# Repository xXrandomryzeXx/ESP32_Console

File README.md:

# ESP32_Console
## Instalation
Following the official documentation from Espressif, you have to setup the standard toolchain for your system:  
[Linux/MacOS](https://docs.espressif.com/projects/esp-idf/en/stable/esp32/get-started/linux-macos-setup.html)  
[Windows](https://docs.espressif.com/projects/esp-idf/en/stable/esp32/get-started/windows-setup.html)  
### Linux/MacOS
After following the documentation you should have the standard toolchain setup.  
Now you can clone the repository. Once inside it, run the command  

`. $HOME/esp/esp-idf/export.sh`  

or for Fish  

`. $HOME/esp/esp-idf/export.fish`  

This will setup the ESP-IDF environment for the project.

Inside the cloned repository should be a directory called `SD_CARD_FILES`.  
Copy its contents to a **Micro SD Card** and format the card to the **FAT32 Format**

After inserting the card into the Micro SD Card Reader, you can build and flash the project to the ESP32  
This is done by performing the following command inside the cloned repository.  

`idf.py build flash monitor`

This will  
1. Build the project
2. Flash it to the ESP
3. Print the debug information to the terminal

### Windows
As I was not developing this on Windows, I don't know how the setup would go for it.

## About
The project was developed as a final assigment for high school. It utilizes the ESP32 to make a console-like game for learning Japanese Kanji.
It consists of multiple components:
1. Custom PCB
2. Node MCU32S board
3. 3.2 Inch TFT SPI Display board
4. Micro SD Card Reader board
5. 4x Push Button
6. 4x 10K resistor
7. Power Swtich
8. Battery box for 3 AAA 1.5V batteries

## The PCB Board
The board is two sided THT. Each component is labeled where it's supposed to be soldered on the board.  
The clean board looks like this  

When attaching the components you have to match their orientation with the text on the silkscreen.  
The populated PCB should look like this

## Game Demonstration
When the console is turned on by the switch in the middle, it will light up and the main menu will show up.  
It displays the Highest achieved score that is saved to the Micro SD Card and also a choice to start a game.  

When you press the corresponding button to the **play** option a new game will begin.  
A question will be generated and the answers selectedd. They will either ask for a  
translation of the kanji displayed or for a reading in japanese.  

If the chosen answer is wrong the game will deduct one life point and will display the  
correct answer for the question.  

Otherwise if the chosen aswer is correct, the game will give 1 point and notify the player  
that the chose answer has been correct.  

The game will end once the player has ran out of lives, there is no way to end a game without
losing unless you power off the console. At the end of a game, the player will be notified
about the score they managed to get. If the score is more than the recorded high score, it will  
be saved as the new highest score.  

## Possible improvements
As this was the first time I ever made something involving a Custom PCB and so many components, I have missed to think about
certain things that could prove beneficial for future projects.

### Cleaner PCB
For a first time design I feel like this one is OK, but for future projects the design should incorporate less prototyping boards and more individual components, like SMD components. These may require more complicated soldering methods but the final product would have a much more professional and clean look.  
Major imporvement would be the use of an independent ESP32 chip that has been flashed with the project.
Another big improvement would come from the TFT display. Instead of using one with a board and pins, an alternative variant that utilises a connector would be better in terms of how thin the console could be.

### Better software
This was also my first time programming on an ESP32 and ESP-IDF, so a lot was figured out through the examples given by Espressif, but the code was not well suited for this project.  
The most improvement that could be done is in the rendering, because the current rendering method is so slow that the FPS is lower than 1, but it can most certainly be at least as good as 10FPS.

### Mounting holes
Mounting holes designed into the PCB could allow for a case to be made for the console, giving it a more solid look and making it a lot more comfortable and safer than the current one, where you hold the PCB and have to take care of what touches the board.

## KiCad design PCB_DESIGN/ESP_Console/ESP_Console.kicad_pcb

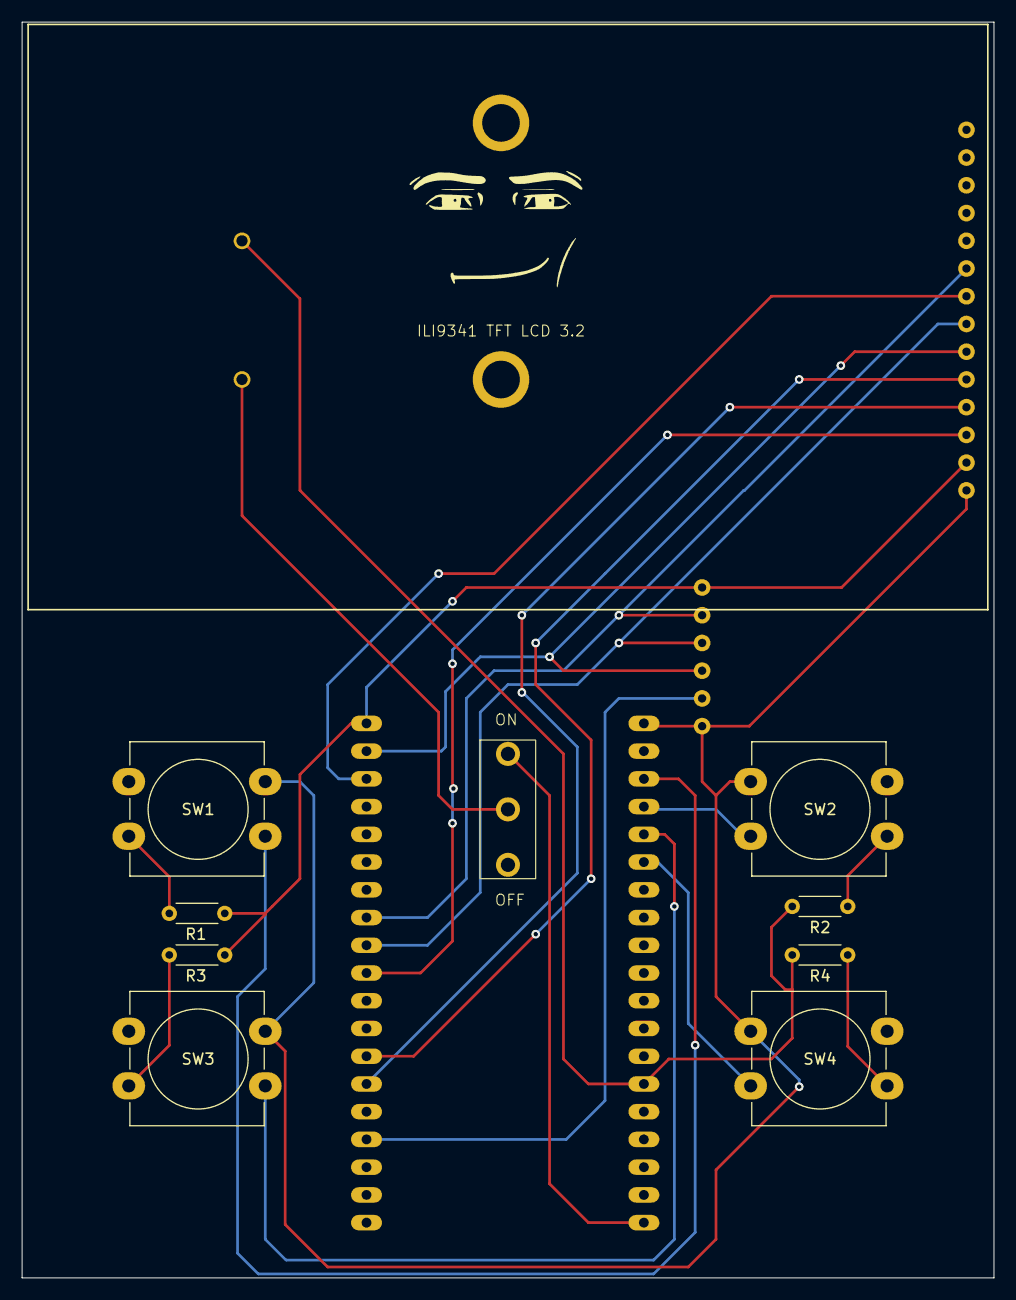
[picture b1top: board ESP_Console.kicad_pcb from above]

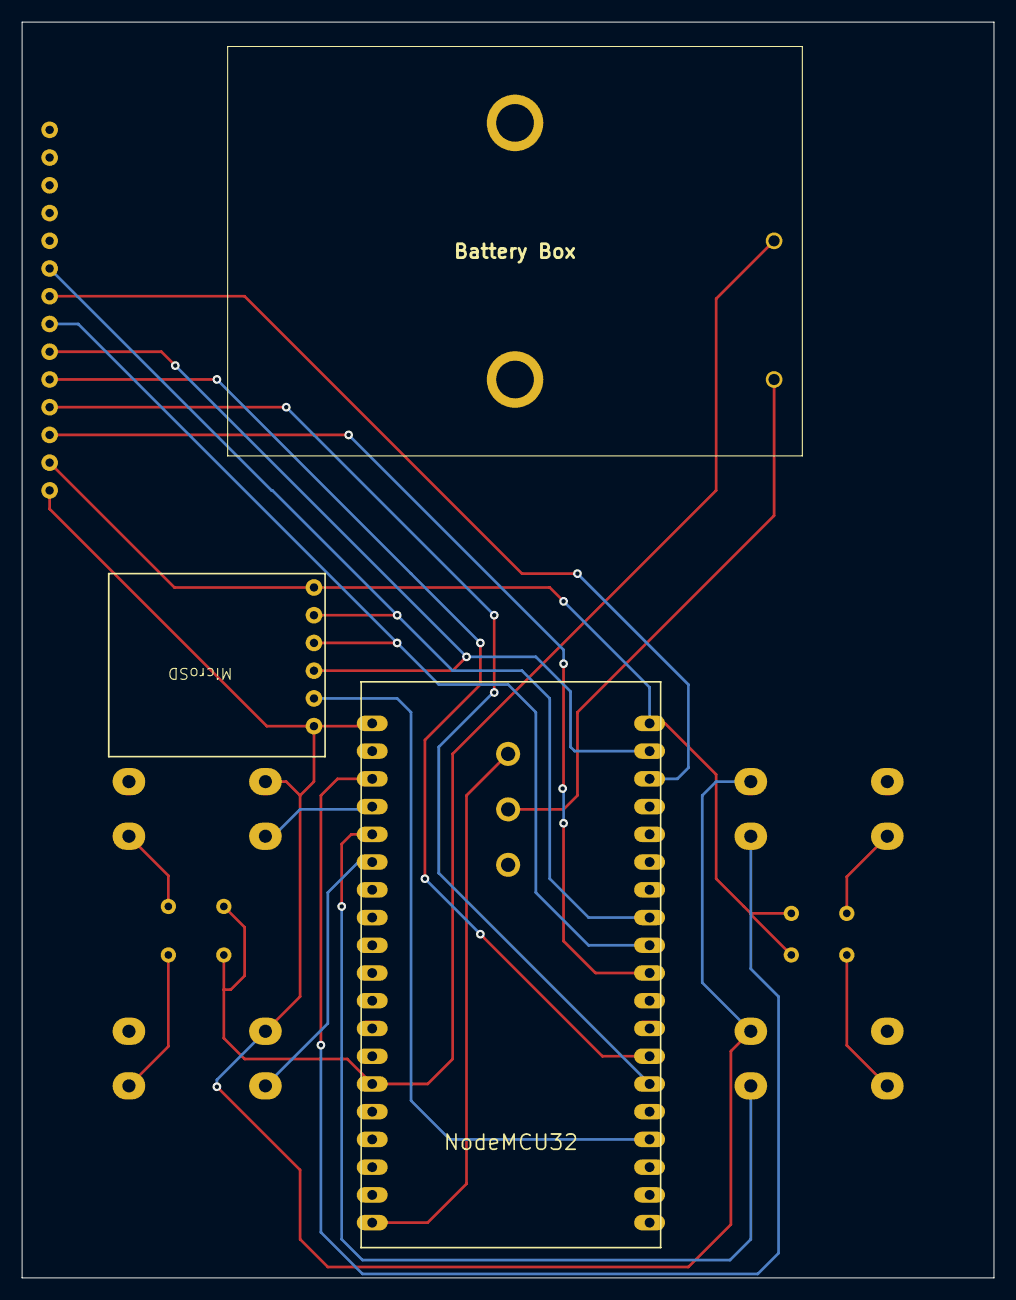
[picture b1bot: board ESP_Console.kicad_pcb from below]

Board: 2 copper layers, 89.0 x 115.0 mm, 13 parts (3 on the bottom side), 17 nets.

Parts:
Battery Box: 2479; 3xAAA battery box 2479
ILI9341 TFT LCD 3.2: 3.2inch SPI Module MSP3218
MicroSD: Micro SD reader module
NodeMCU32: NODEMCU32S
R1, R2, R3, R4: R_US; R_Axial_DIN0204_L3.6mm_D1.6mm_P5.08mm_Horizontal
SW1, SW2, SW3, SW4: SW_Push_Open_Dual; SW_PUSH-12mm_Wuerth-430476085716
SW_1P2T1: SW_1P2T

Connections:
GND: ILI9341 TFT LCD 3.2.2 (GND), MicroSD.6 (GND), NodeMCU32.GND@2, R1.2, R3.2
unnamed: NodeMCU32.GPIO36, R1.1, SW1.2
unnamed: NodeMCU32.GPIO39, R2.1, SW2.2
unnamed: NodeMCU32.GPIO34, R3.1, SW3.2
unnamed: NodeMCU32.GPIO35, R4.1, SW4.2
unnamed: Battery Box.1 (+), SW_1P2T1.1 (VCC)
unnamed: ILI9341 TFT LCD 3.2.1 (VCC), MicroSD.1 (3v3), NodeMCU32.3V3 (3.3V), SW1.1, SW2.1, SW3.1, SW4.1
unnamed: Battery Box.2 (-), NodeMCU32.GND@1, R2.2, R4.2
unnamed: ILI9341 TFT LCD 3.2.7 (SCK), MicroSD.4 (CLK), NodeMCU32.GPIO18
unnamed: MicroSD.2 (CS), NodeMCU32.GPIO15
unnamed: ILI9341 TFT LCD 3.2.9 (MISO), MicroSD.5 (MISO), NodeMCU32.GPIO19
unnamed: ILI9341 TFT LCD 3.2.6 (MOSI), MicroSD.3 (MOSI), NodeMCU32.GPIO23
unnamed: ILI9341 TFT LCD 3.2.3 (CS), NodeMCU32.GPIO5
unnamed: ILI9341 TFT LCD 3.2.5 (DC), NodeMCU32.GPIO4
unnamed: ILI9341 TFT LCD 3.2.8 (LED), NodeMCU32.GPIO22
unnamed: ILI9341 TFT LCD 3.2.4 (RST), NodeMCU32.GPIO0
VCC: NodeMCU32.VIN, SW_1P2T1.2 (Out_1)

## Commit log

2024-02-14 Removed previous README
2024-02-14 Text can be printed on the screen
2024-02-17 Can print out japanese text to the LCD (hiragana only)
2024-02-17 Created game loop and started work on the state machine
2024-02-19 State machine works, loading desired background image from SD is possible
2024-02-22 Started work on Question generation. Don't run yet! It clears the kanji.txt file clean, and I don't know why
2024-03-21 Some code refactoring, new file to handle random number generation. Question generation is not working. The array of answers gets cleared randomly
2024-03-24 Delete build directory
    These files are not needed for building the project, they are generated when the project is built.
2024-03-26 Japanese texts draw without a problem. Parentheses draw in Japanese text cleanly. Question generation is ALMOST done.
2024-03-27 When in the game, the text for the answers will draw in it's respective positions. Needs more work.
2024-03-29 Answering a question creates a new one. Fixed memory leak when loading an image
2024-04-02 Answers in english get pushed to the side of the screen with 20 px padding. Wrong and Right answers are announced with a respective sprite
2024-04-05 All answers have a padding of 20px. There is a counter for the correct answers for the future implementation of the score, some functions have been removed and others have taken their job
2024-04-08 Lives can be tracked. End of game will be reached when the lives reach 0. setState was changed to set_state
2024-04-09 Game loop completes. There is a memory leak that causes the memory to run out after 2 retries. Needs high score to be saved and loaded and the memory leak to be fixed!
2024-04-12 Memory leak fixed! Final score can be viewed at the end of the game. High score save and load is left to be done
2024-04-16 High score load and save complete. Questions use all posible answers, not just the first one
2024-04-16 Removed Quit option from the main menu
2024-04-18 Removed unused code, added descriptions to all functions in the header files
2024-09-17 Fixed the problem where you cannot play another game after finishing one
2024-09-17 Added PCB Design files
2024-09-17 Added pictures for the README
2024-09-18 More pictures for the Readme added
2024-09-18 Rename QuestionFailed.jpg to QuestionWrong.jpg
